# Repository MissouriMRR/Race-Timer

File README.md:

# Overview

This repository contains the PCB files for the PIDFlight Lap PCB files and CAD files.

# Features

-Using the PIDFlight software these timers can
  -Connect to an external device running the Software via bluetooth
  -keep track of multiple drones, using physical and digital timers

#### Physical

- Expected Size: 150mm x 150mm
- Rectangular shape
- Screw Mounting Holes 

#### Primary Components

- Arduino Nano x4
- RX5808 x4
- HC_06 x4
- 1k Ohm resistors x12

#### Power

- Connection to LiPo Packs
- switch spot to remove power when not in use

# Companion Documentation

RX5808 Datasheet: https://www.foxtechfpv.com/product/5.8G%20modules/rx5808/RX5808-Spec-V1.pdf 

HC_06 Bluetooth Module Datasheet: https://components101.com/wireless/hc-06-bluetooth-module-pinout-datasheet

PIDFlight Lap Website: https://www.pidflight.com/pidflight-lap/rev02/

   -Schematic from website: file:///C:/Users/c0nn0/Downloads/PIDflight-Lap-Timing-Schematic-Revision-01.pdf
      
   -Communication Wiring Diagram from website: https://www.pidflight.com/pidflight-lap/multipilot/

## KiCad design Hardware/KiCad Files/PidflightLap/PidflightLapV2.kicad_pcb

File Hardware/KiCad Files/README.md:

The PIDFlight lap is the PCB files the other folders are for component footprints and symbols

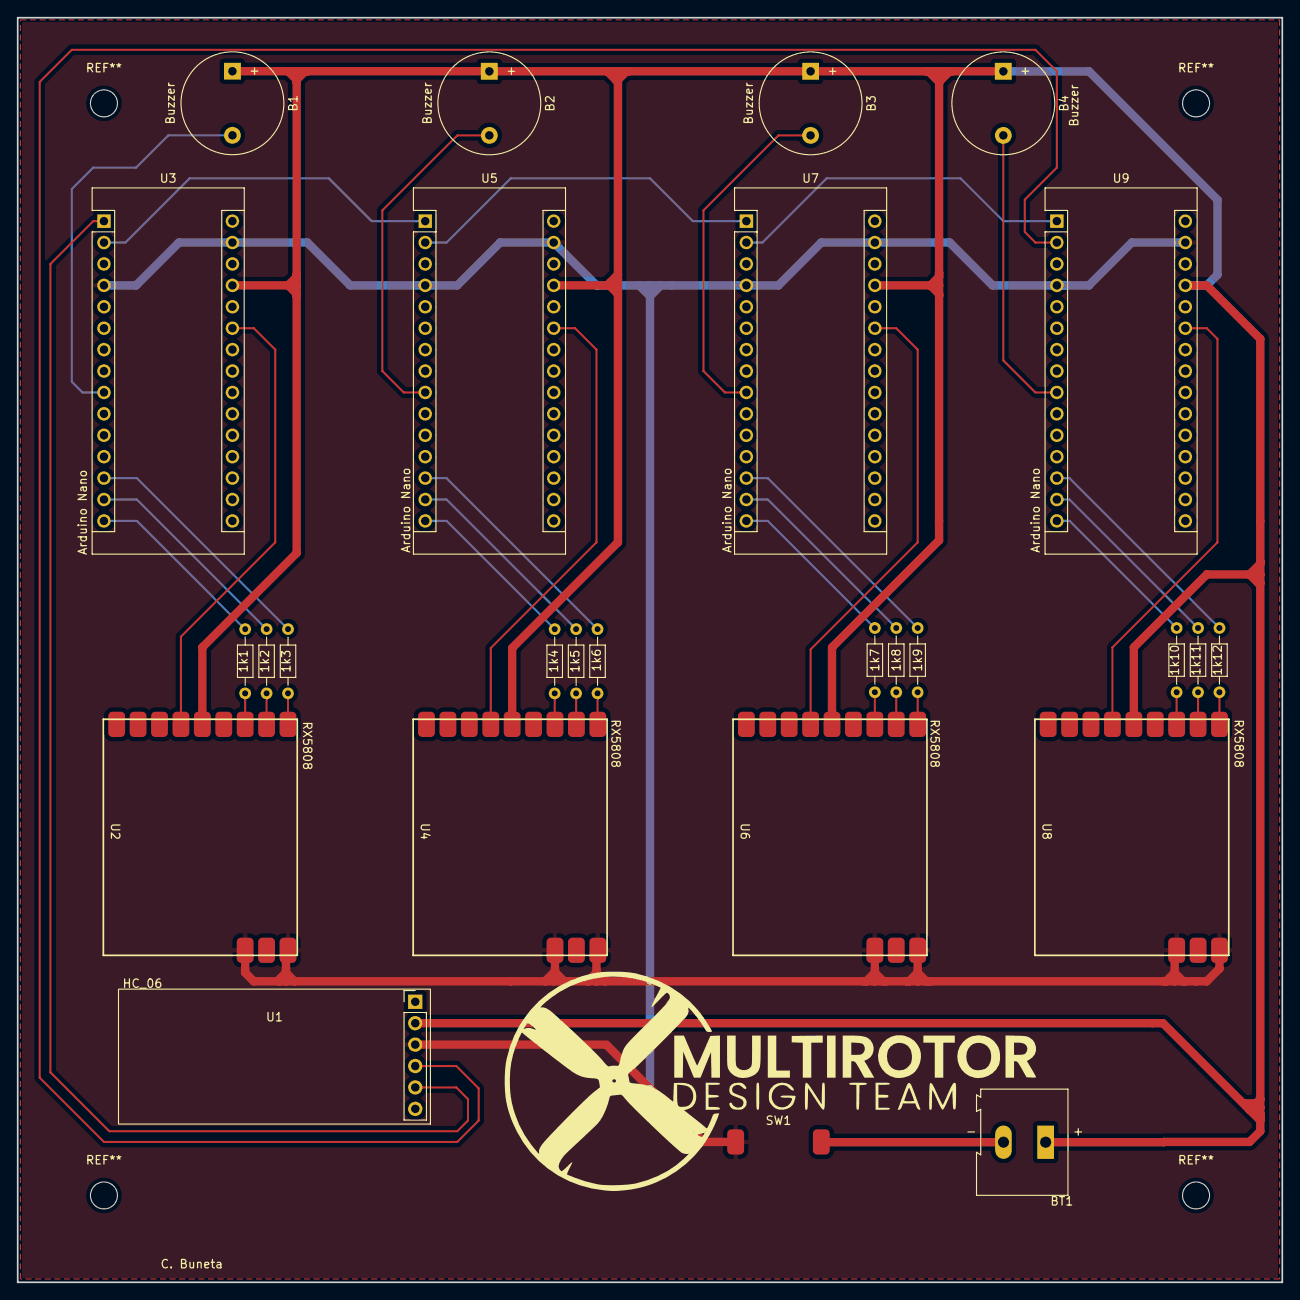
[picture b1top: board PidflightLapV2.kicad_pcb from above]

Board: 2 copper layers, 150.0 x 150.0 mm, 28 parts (0 on the bottom side), 40 nets.

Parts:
1k1: R1; R_Axial_DIN0204_L3.6mm_D1.6mm_P7.62mm_Horizontal
1k2: R2; R_Axial_DIN0204_L3.6mm_D1.6mm_P7.62mm_Horizontal
1k3: R3; R_Axial_DIN0204_L3.6mm_D1.6mm_P7.62mm_Horizontal
1k4: R4; R_Axial_DIN0204_L3.6mm_D1.6mm_P7.62mm_Horizontal
1k5: R5; R_Axial_DIN0204_L3.6mm_D1.6mm_P7.62mm_Horizontal
1k6: R6; R_Axial_DIN0204_L3.6mm_D1.6mm_P7.62mm_Horizontal
1k7: R7; R_Axial_DIN0204_L3.6mm_D1.6mm_P7.62mm_Horizontal
1k8: R8; R_Axial_DIN0204_L3.6mm_D1.6mm_P7.62mm_Horizontal
1k9: R9; R_Axial_DIN0204_L3.6mm_D1.6mm_P7.62mm_Horizontal
1k10: R10; R_Axial_DIN0204_L3.6mm_D1.6mm_P7.62mm_Horizontal
1k11: R11; R_Axial_DIN0204_L3.6mm_D1.6mm_P7.62mm_Horizontal
1k12: R12; R_Axial_DIN0204_L3.6mm_D1.6mm_P7.62mm_Horizontal
B1, B2, B3, B4: Buzzer; Buzzer_12x9.5RM7.6
BT1: Battery; TerminalBlock_Altech_AK300-2_P5.00mm
G: LOGO; multirotorwordsfootprint
SW1: SW_SPST; SMD Solder Pads
U1: HC_06; HC_06 Bluetooth Module
U2, U4, U6, U8: RX5808
U3, U5, U7, U9: Arduino_Nano_v3.x; Arduino_Nano

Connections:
+5V: B1.1 (V+), B2.1 (V+), B3.1 (V+), B4.1 (V+), BT1.1 (+), U1.2 (VCC), U2.5 (5V), U3.27 (+5V), U4.5 (5V), U5.27 (+5V), U6.5 (5V), U7.27 (+5V), U8.5 (5V), U9.27 (+5V)
GND: SW1.1 (A), U1.3 (GND), U2.10 (GND), U2.12 (GND), U3.4 (GND), U3.29 (GND), U4.10 (GND), U4.12 (GND), U5.4 (GND), U5.29 (GND), U6.10 (GND), U6.12 (GND), U7.4 (GND), U7.29 (GND), U8.10 (GND), U8.12 (GND), U9.4 (GND), U9.29 (GND)
unnamed: 1k1.1, U3.15 (D12)
unnamed: 1k1.2, U2.7 (CH3)
unnamed: 1k2.1, U3.14 (D11)
unnamed: 1k2.2, U2.8 (CH2)
unnamed: 1k3.1, U3.13 (D10)
unnamed: 1k3.2, U2.9 (CH1)
unnamed: 1k4.1, U5.15 (D12)
unnamed: 1k4.2, U4.7 (CH3)
unnamed: 1k5.1, U5.14 (D11)
unnamed: 1k5.2, U4.8 (CH2)
unnamed: 1k6.1, U5.13 (D10)
unnamed: 1k6.2, U4.9 (CH1)
unnamed: 1k7.1, U7.15 (D12)
unnamed: 1k7.2, U6.7 (CH3)
unnamed: 1k8.1, U7.14 (D11)
unnamed: 1k8.2, U6.8 (CH2)
unnamed: 1k9.1, U7.13 (D10)
unnamed: 1k9.2, U6.9 (CH1)
unnamed: 1k10.1, U9.15 (D12)
unnamed: 1k10.2, U8.7 (CH3)
unnamed: 1k11.1, U9.14 (D11)
unnamed: 1k11.2, U8.8 (CH2)
unnamed: 1k12.1, U9.13 (D10)
unnamed: 1k12.2, U8.9 (CH1)
unnamed: B1.2 (V-), U3.9 (D6)
unnamed: B2.2 (V-), U5.9 (D6)
unnamed: B3.2 (V-), U7.9 (D6)
unnamed: B4.2 (V-), U9.9 (D6)
unnamed: BT1.2 (-), SW1.2 (B)
unnamed: U1.4 (TXD), U9.2 (D0/RX)
unnamed: U1.5 (RXD), U3.1 (D1/TX)
unnamed: U2.4 (RSSI), U3.25 (A6)
unnamed: U3.2 (D0/RX), U5.1 (D1/TX)
unnamed: U4.4 (RSSI), U5.25 (A6)
unnamed: U5.2 (D0/RX), U7.1 (D1/TX)
unnamed: U6.4 (RSSI), U7.25 (A6)
unnamed: U7.2 (D0/RX), U9.1 (D1/TX)
unnamed: U8.4 (RSSI), U9.25 (A6)

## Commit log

2022-09-19 Added example Readme
    This is a test
2022-09-19 Updated README
    Fixed the readme to contain relevent information to the board and the PIDFlight project.
2022-09-19 Fixed README formatting
    Fixed mistakes in the readme formatting
2022-09-19 Deleted test.txt
    removing test file
2022-09-20 Added KiCAD Files
2022-09-30 Cleaned Up Files and added Bevels and BOM
    removed some pointless KiCAD files I had accidently added created as well as beveled all the 90 degree connections on the PCB file
2022-10-01 Add files via upload
    Version 2 with every added feature. (Needs to be changed upon request for certain sizing requirements)
2022-10-02 Added Gerber Files
2022-10-15 Version 3 of PCB Box Design
    Some more slight changes to the PCB Box design. I also added the locking cad file as well as a cad file for a switch.
2023-01-25 Add files via upload
    This version has an updated text font that won't look wacky.
2023-01-25 Updated Font That Don't Look Wack
2023-01-27 Add files via upload
    Slide Lid and Body With Logo Will Change If Necessary.
